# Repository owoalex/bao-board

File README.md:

# bao-board
Experimental BLDC driver board based on the RP2040.
Compatible with the open source [v3fkontroller](https://github.com/owoalex/v3fkontroller) firmware.

## BOM for v1.3
| Part                                              | Mfr Part No        | #  | GBP   | Total | Refs    |
| ------------------------------------------------- | ------------------ | -- | ----- | ----- | ------- |
| RS PRO 10μF Axial Electrolytic Capacitor 35V      | 707-6391           |  3 |  0.26 |  0.78 | C1-3    |
| Murata 1μF Multilayer Ceramic Capacitor 1uF 50V   | RCER71H105K2K1H03B |  3 |  0.56 |  1.67 | C4-6    |
| 100pF 1206 SMD Capacitors                         | GENERIC            |  2 |  0.05 |  0.10 | C7-8    |
| RS PRO 100μF Axial Electrolytic Capacitor 100V    | 707-6552           |  1 |  1.01 |  1.01 | C9      |
| RS PRO 1000μF Axial Electrolytic Capacitor 25V    | 707-6650           |  1 |  0.92 |  0.92 | C10     |
| STTH2R06 Rectifier (PN) Diode 600V 2A             | STTH2R06           |  3 |  0.55 |  1.66 | D1-3    |
| STM 150V 3A Schottky Diode DO-201AD               | STPS3150RL         |  1 |  0.37 |  0.37 | D4      |
| Kingbright 2.2 V Green LED 3216 (1206) SMD        | KP-3216SGC         |  2 |  0.18 |  0.36 | D5-6    |
| ASSMANN Socket Type B 2.0 USB Connector           | A-USBSB            |  1 |  1.29 |  1.29 | J1      |
| RS PRO 100uH 3A IDC Inductor                      | 104-8436           |  1 |  0.99 |  0.99 | L1      |
| Infineon 75V 80A N-Channel MOSFET (TO-220)        | IRFB3607PBF        | 12 |  1.07 | 12.84 | Q1-12   |
| TE Connectivity 1kΩ Carbon Film Resistor 0.33W    | CFR25J1K0          |  6 |  0.12 |  0.74 | R1-6    |
| 33Ω 1206 SMD Resistors                            | GENERIC            |  2 |  0.05 |  0.10 | R7-8    |
| 100Ω 1206 SMD Resistors                           | GENERIC            |  4 |  0.05 |  0.20 | R9-12   |
| 1kΩ 1206 SMD Resistors                            | GENERIC            |  2 |  0.05 |  0.10 | R13-14  |
| Red Button Tactile Switch SPST                    | 479-1429           |  1 |  0.13 |  0.13 | SW1     |
| Infineon 20V MOSFET/IGBT Driver 28-Pin PDIP       | IR2130PBF          |  1 | 12.45 | 12.45 | U1      |
| Winslow 28-Way IC Dip Socket 0.6in Pitch          | W3128TRC           |  1 |  0.17 |  0.17 | (U1)    |
| Raspberry Pi RP2040                               | RP2040             |  1 |  0.85 |  0.85 | U2      |
| DiodesZetex 3.3V 1A Linear Regulator (SOT-223)    | AZ1117H-3.3TRE1    |  1 |  0.10 |  0.10 | U3      |
| TI Buck Converter 12V 3A (5-Pin TO-220)           | LM2576HVT-12       |  1 |  7.82 |  7.82 | U4      |
| Winbond 16Mb SPI Flash                            | W25Q16JVSNIQ       |  1 |  0.67 |  0.67 | U5      |
| STM 5V 1A Pos LDO Regulator (TO-220)              | L7805ACV           |  1 |  0.76 |  0.76 | U6      |
| QANTEK 12MHz Crystal (HC-49/U-S)                  | QCL12.0000F18B23B  |  1 |  0.16 |  0.16 | Y1      |

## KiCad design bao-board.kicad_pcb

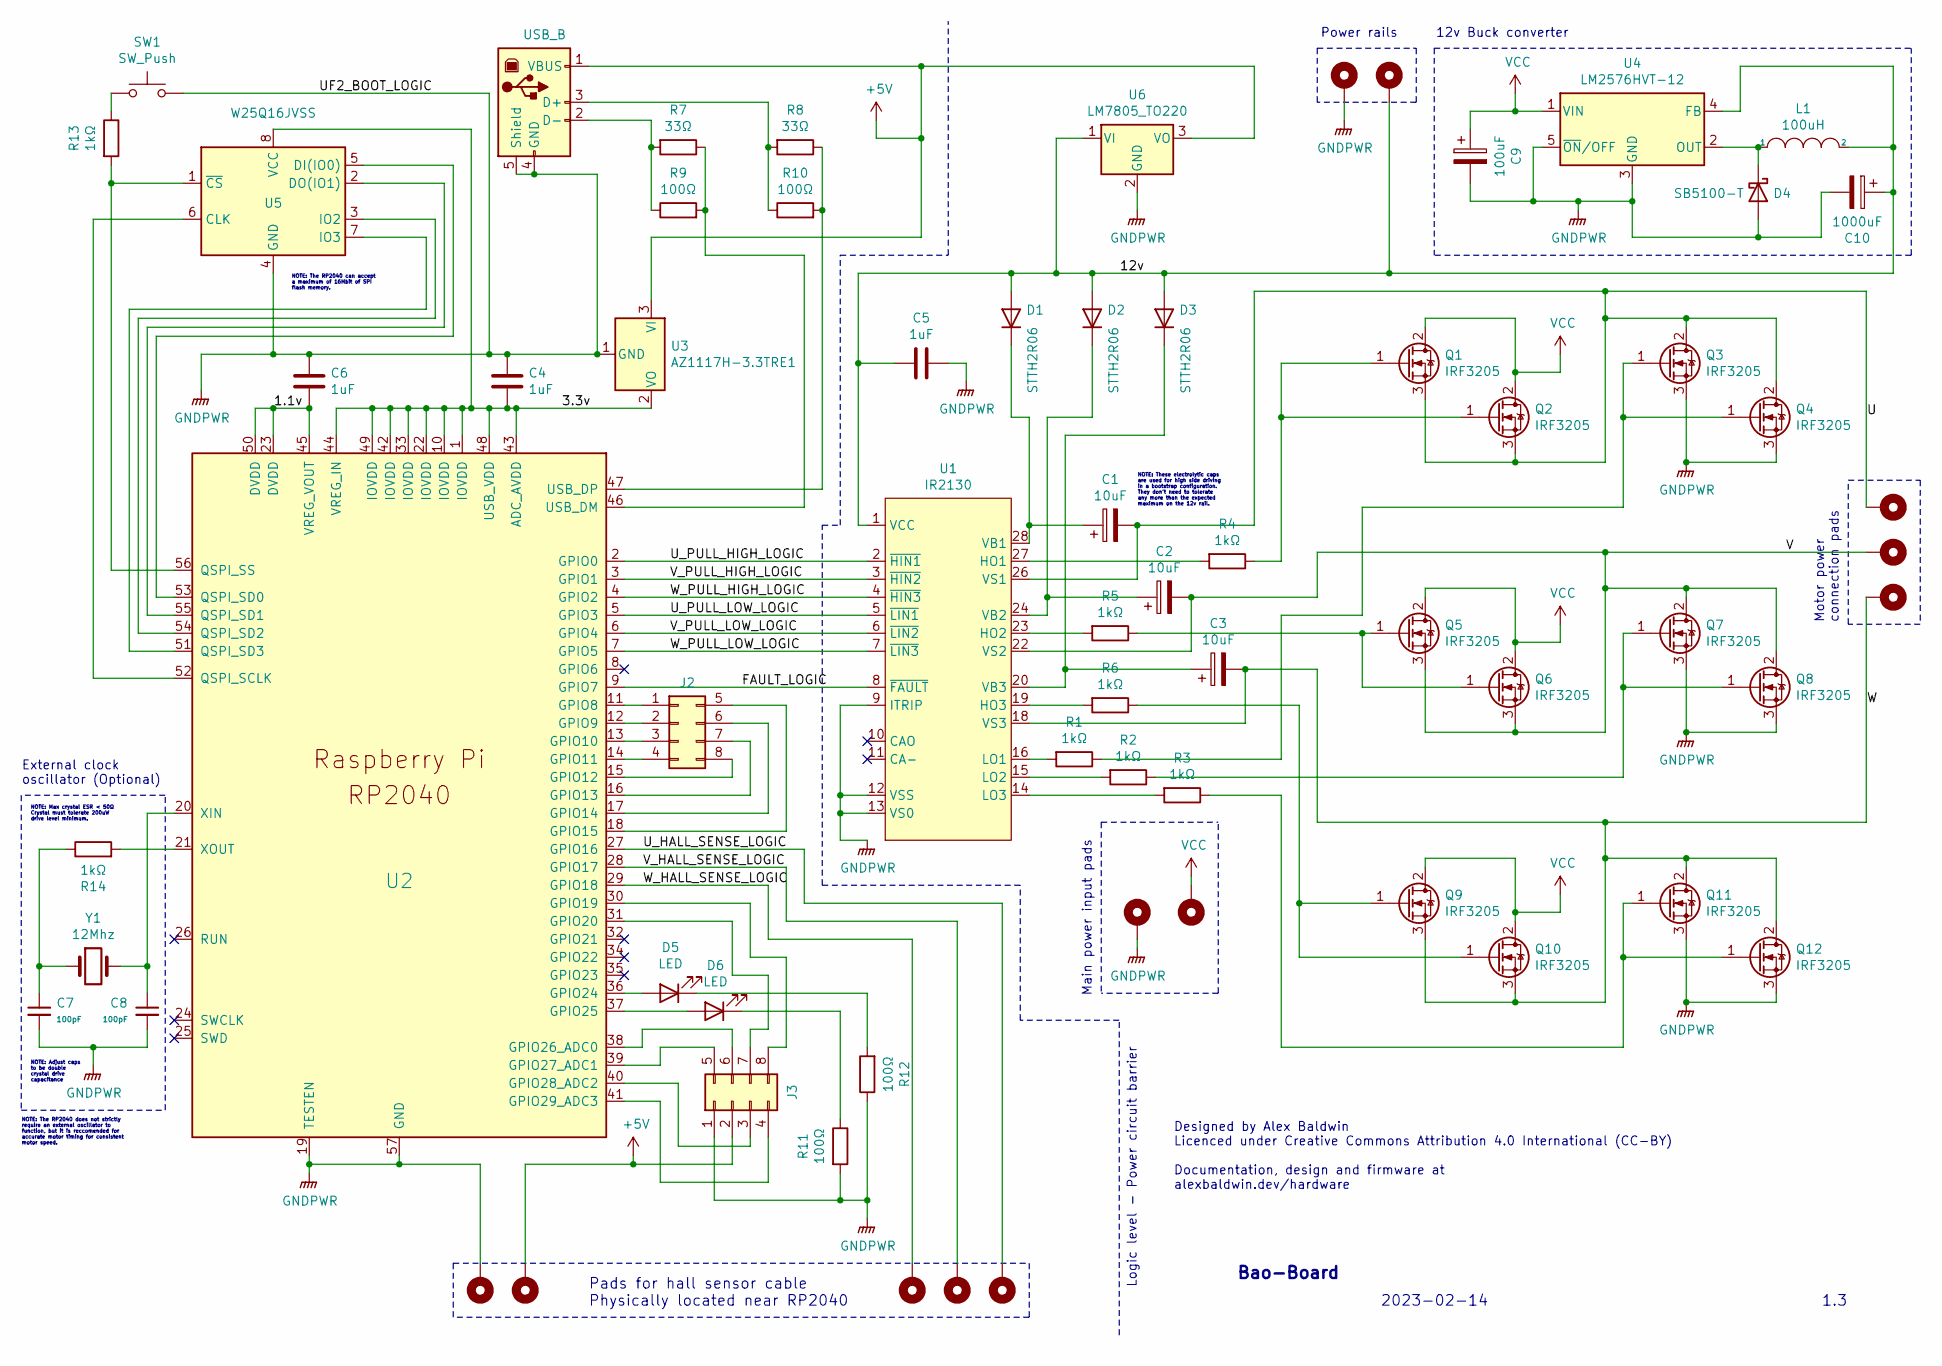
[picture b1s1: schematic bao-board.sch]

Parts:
C1, C2, C3: 10uF; CP_Axial_L18.0mm_D6.5mm_P25.00mm_Horizontal
C4, C5, C6: 1uF; C_Rect_L7.0mm_W2.0mm_P5.00mm
C7, C8: 100pF; C_1206_3216Metric_Pad1.33x1.80mm_HandSolder
C9: 100uF; CP_Axial_L18.0mm_D6.5mm_P25.00mm_Horizontal
C10: 1000uF; CP_Axial_L25.0mm_D10.0mm_P30.00mm_Horizontal
D1, D2, D3: STTH2R06; D_T-1_P10.16mm_Horizontal
D4: SB5100-T; D_DO-201AD_P15.24mm_Horizontal
D5, D6: LED; LED_1206_3216Metric_Pad1.42x1.75mm_HandSolder
H1, H2, H3, H4, H5: MountingHole_Pad; MountingHole_3mm_Pad_Via
H6, H7, H8, H9, H10: MountingHole_Pad; TestPoint_THTPad_D2.0mm_Drill1.0mm
H11, H13: MountingHole_Pad; MountingHole_2.2mm_M2_Pad_Via
J1: USB_B; USB_B_OST_USB-B1HSxx_Horizontal
J2, J3: Conn_02x04_Top_Bottom; PinHeader_2x04_P2.54mm_Vertical
L1: 100uH; THT Toroidal Inductor Horizontal 25x12mm
Q1, Q2, Q3, Q4, Q5, Q6, Q7, Q8, Q9, Q10, Q11, Q12: IRF3205; TO-220-3_Horizontal_TabUp
R1, R2, R3, R4, R5, R6: 1kΩ; R_Axial_DIN0207_L6.3mm_D2.5mm_P10.16mm_Horizontal
R7, R8: 33Ω; R_1206_3216Metric_Pad1.30x1.75mm_HandSolder
R9, R10, R11, R12: 100Ω; R_1206_3216Metric_Pad1.30x1.75mm_HandSolder
R13, R14: 1kΩ; R_1206_3216Metric_Pad1.30x1.75mm_HandSolder
SW1: SW_Push; SW_PUSH_6mm
U1: IR2130; DIP-28_W15.24mm
U2: RP2040
U3: AZ1117H-3.3TRE1; SOT-223-3_TabPin2
U4: LM2576HVT-12; TO-220-5_P3.4x3.8mm_StaggerEven_Lead7.13mm_TabDown
U5: W25Q16JVSS; SOIC-8_3.9x4.9mm_P1.27mm
U6: LM7805_TO220; TO-220-3_Horizontal_TabDown
Y1: 12Mhz; Crystal_HC49-U_Vertical

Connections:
+5V: H9.1, J1.1 (VBUS), J3.2, U3.3 (VI), U6.3 (VO)
/1.1v: C6.2, U2.23 (DVDD), U2.45 (VREG_VOUT), U2.50 (DVDD)
/3.3v: C4.2, U2.1 (IOVDD), U2.10 (IOVDD), U2.22 (IOVDD), U2.33 (IOVDD), U2.42 (IOVDD), U2.43 (ADC_AVDD), U2.44 (VREG_IN), U2.48 (USB_VDD), U2.49 (IOVDD), U3.2 (VO), U5.8 (VCC)
/12v: C5.1, C10.1, D1.2 (A), D2.2 (A), D3.2 (A), H13.1, L1.2, U1.1 (VCC), U4.4 (FB), U6.1 (VI)
/FAULT_LOGIC: U1.8 (~FAULT), U2.9 (GPIO7)
/U: C1.2, H1.1, Q1.3 (S), Q2.3 (S), Q3.2 (D), Q4.2 (D), U1.26 (VS1)
/U_HALL_SENSE_LOGIC: H6.1, U2.27 (GPIO16)
/U_PULL_HIGH_LOGIC: U1.2 (~HIN1), U2.2 (GPIO0)
/U_PULL_LOW_LOGIC: U1.5 (~LIN1), U2.5 (GPIO3)
/V: C2.2, H2.1, Q5.3 (S), Q6.3 (S), Q7.2 (D), Q8.2 (D), U1.22 (VS2)
/V_HALL_SENSE_LOGIC: H7.1, U2.28 (GPIO17)
/V_PULL_HIGH_LOGIC: U1.3 (~HIN2), U2.3 (GPIO1)
/V_PULL_LOW_LOGIC: U1.6 (~LIN2), U2.6 (GPIO4)
/W: C3.2, H3.1, Q9.3 (S), Q10.3 (S), Q11.2 (D), Q12.2 (D), U1.18 (VS3)
/W_HALL_SENSE_LOGIC: H8.1, U2.29 (GPIO18)
/W_PULL_HIGH_LOGIC: U1.4 (~HIN3), U2.4 (GPIO2)
/W_PULL_LOW_LOGIC: U1.7 (~LIN3), U2.7 (GPIO5)
GNDPWR: C4.1, C5.2, C6.1, C7.2, C8.2, C9.2, C10.2, D4.2 (A), H5.1, H10.1, H11.1, J1.4 (GND), J1.5 (Shield), J3.1, Q3.3 (S), Q4.3 (S), Q7.3 (S), Q8.3 (S), Q11.3 (S), Q12.3 (S), R11.2, R12.1, SW1.2, U1.9 (ITRIP), U1.12 (VSS), U1.13 (VS0), U2.19 (TESTEN), U2.57 (GND), U3.1 (GND), U4.3 (GND), U4.5 (~ON~/OFF), U5.4 (GND), U6.2 (GND)
unnamed: C1.1, D1.1 (K), U1.28 (VB1)
unnamed: C2.1, D2.1 (K), U1.24 (VB2)
unnamed: C3.1, D3.1 (K), U1.20 (VB3)
unnamed: C7.1, R14.1, Y1.1
unnamed: C8.1, U2.20 (XIN), Y1.2
unnamed: D4.1 (K), L1.1, U4.2 (OUT)
unnamed: D5.1 (K), R12.2
unnamed: D5.2 (A), U2.36 (GPIO24)
unnamed: D6.1 (K), R11.1
unnamed: D6.2 (A), U2.37 (GPIO25)
unnamed: J1.2 (D-), R7.2, R9.1
unnamed: J1.3 (D+), R8.2, R10.1
unnamed: J2.1, U2.11 (GPIO8)
unnamed: J2.2, U2.12 (GPIO9)
unnamed: J2.3, U2.13 (GPIO10)
unnamed: J2.4, U2.14 (GPIO11)
unnamed: J2.5, U2.18 (GPIO15)
unnamed: J2.6, U2.17 (GPIO14)
unnamed: J2.7, U2.16 (GPIO13)
unnamed: J2.8, U2.15 (GPIO12)
unnamed: J3.3, U2.40 (GPIO28_ADC2)
unnamed: J3.4, U2.41 (GPIO29_ADC3)
unnamed: J3.5, U2.39 (GPIO27_ADC1)
unnamed: J3.6, U2.38 (GPIO26_ADC0)
unnamed: J3.7, U2.31 (GPIO20)
unnamed: J3.8, U2.30 (GPIO19)
unnamed: Q1.1 (G), Q2.1 (G), R4.1
unnamed: Q3.1 (G), Q4.1 (G), R1.1
unnamed: Q5.1 (G), Q6.1 (G), R5.1
unnamed: Q7.1 (G), Q8.1 (G), R2.1
unnamed: Q9.1 (G), Q10.1 (G), R6.1
unnamed: Q11.1 (G), Q12.1 (G), R3.1
unnamed: R1.2, U1.16 (LO1)
unnamed: R2.2, U1.15 (LO2)
unnamed: R3.2, U1.14 (LO3)
unnamed: R4.2, U1.27 (HO1)
unnamed: R5.2, U1.23 (HO2)
unnamed: R6.2, U1.19 (HO3)
unnamed: R7.1, R9.2, U2.46 (USB_DM)
unnamed: R8.1, R10.2, U2.47 (USB_DP)
unnamed: R13.1, SW1.1
unnamed: R13.2, U2.56 (QSPI_SS), U5.1 (~CS)
unnamed: R14.2, U2.21 (XOUT)
unnamed: U2.51 (QSPI_SD3), U5.7 (IO3)
unnamed: U2.52 (QSPI_SCLK), U5.6 (CLK)
unnamed: U2.53 (QSPI_SD0), U5.5 (DI(IO0))
unnamed: U2.54 (QSPI_SD2), U5.3 (IO2)
unnamed: U2.55 (QSPI_SD1), U5.2 (DO(IO1))
VCC: C9.1, H4.1, Q1.2 (D), Q2.2 (D), Q5.2 (D), Q6.2 (D), Q9.2 (D), Q10.2 (D), U4.1 (VIN)

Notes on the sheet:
Designed by Alex Baldwin Licenced under Creative Commons Attribution 4.0 International (CC-BY) Documentation, design and firmware at alexbaldwin.dev/hardware
Bao-Board
1.3
2023-02-14
NOTE: Max crystal ESR < 50Ω Crystal must tolerate 200uW drive level minimum.
NOTE: Adjust caps to be double crystal drive capacitance
Pads for hall sensor cable Physically located near RP2040
Main power input pads
Motor power connection pads
Logic level - Power circuit barrier
12v Buck converter
NOTE: The RP2040 can accept a maximum of 16Mbit of SPI flash memory.
NOTE: These electrolytic caps are used for high side driving in a bootstrap configuration. They don't need to tolerate any more than the expected maximum on the 12v rail.
NOTE: The RP2040 does not strictly require an external oscillator to function, but it is reccomended for accurate motor timing for consistent motor speed.
External clock oscillator (Optional)
Power rails

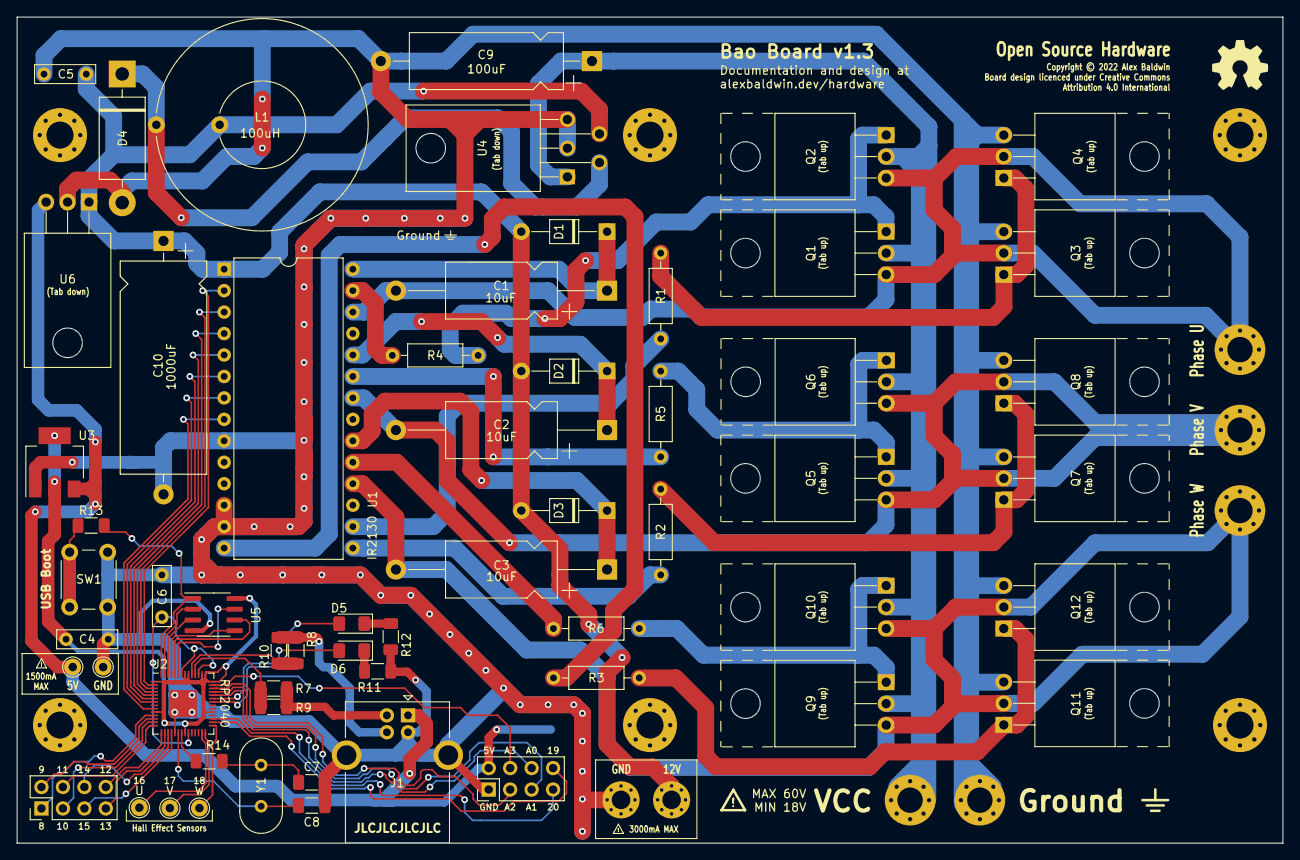
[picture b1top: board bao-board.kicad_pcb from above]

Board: 2 copper layers, 149.9 x 97.8 mm, 66 parts (0 on the bottom side), 67 nets.

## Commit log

2023-01-18 Initial work
2023-01-19 Updated to expose analog inputs instead of using for motor hall. Refined track routing
2023-02-15 Design refinement for v1.3
2023-02-15 Updated some components
2023-02-16 Slightly revised design, version sent of to fab

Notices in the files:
bao-board.kicad_pcb:
Copyright © 2022 Alex Baldwin
Board design licenced under Creative Commons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
